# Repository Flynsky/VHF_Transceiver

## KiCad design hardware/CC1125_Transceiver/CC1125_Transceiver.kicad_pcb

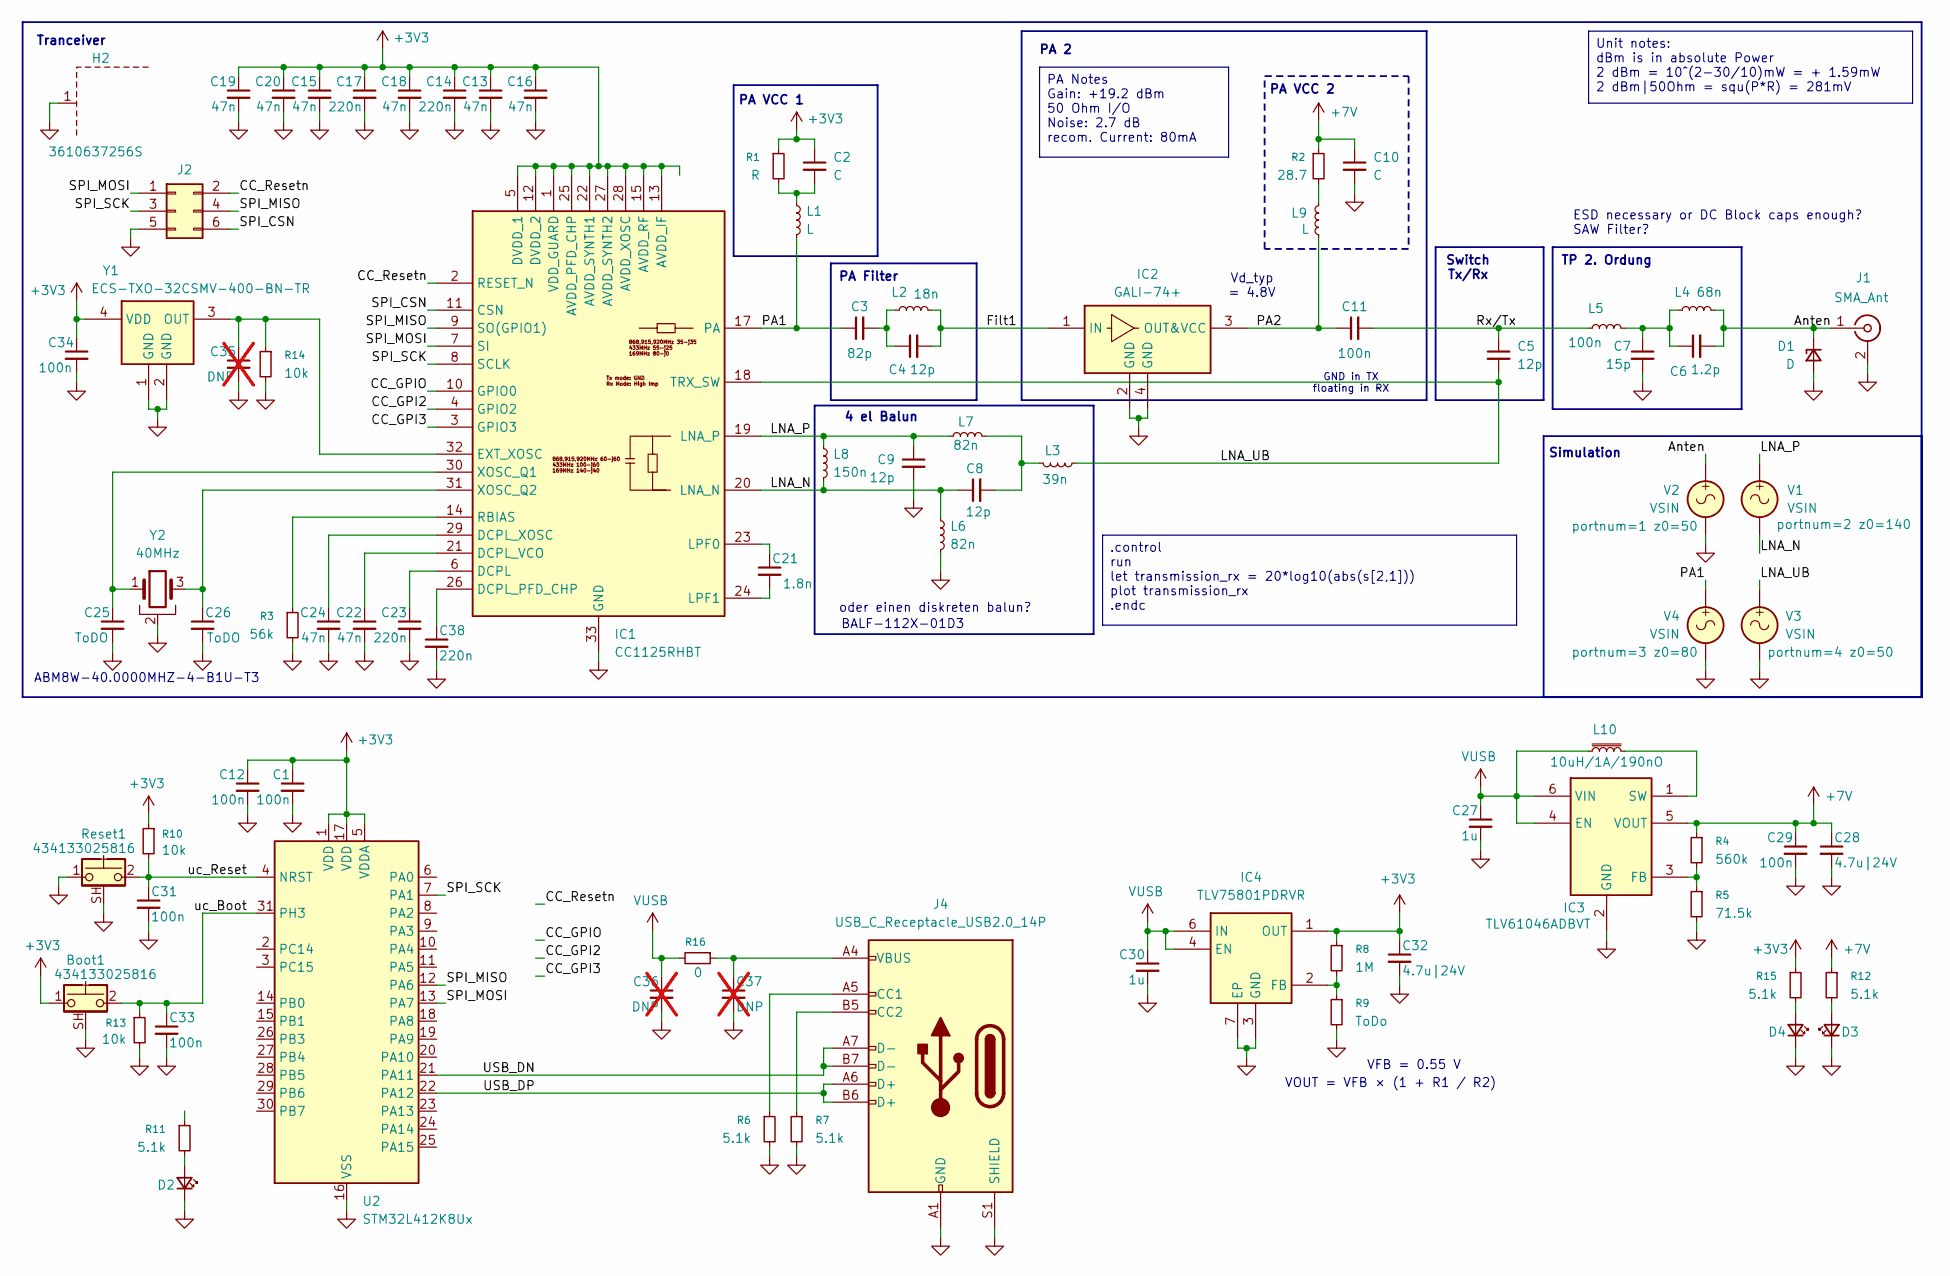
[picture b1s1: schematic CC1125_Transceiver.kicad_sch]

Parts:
Boot1: 434133025816
C1, C11, C12, C29, C31, C33, C34: 100n; C_0402_1005Metric_Pad0.74x0.62mm_HandSolder
C2, C10: C; C_0402_1005Metric_Pad0.74x0.62mm_HandSolder
C3: 82p; C_0402_1005Metric_Pad0.74x0.62mm_HandSolder
C4, C5, C8, C9: 12p; C_0402_1005Metric_Pad0.74x0.62mm_HandSolder
C6: 1.2p; C_0402_1005Metric_Pad0.74x0.62mm_HandSolder
C7: 15p; C_0402_1005Metric_Pad0.74x0.62mm_HandSolder
C13, C15, C16, C18, C19, C20, C22, C24: 47n; C_0402_1005Metric_Pad0.74x0.62mm_HandSolder
C14, C17, C23, C38: 220n; C_0402_1005Metric_Pad0.74x0.62mm_HandSolder
C21: 1.8n; C_0402_1005Metric_Pad0.74x0.62mm_HandSolder
C25, C26: ToDO; C_0402_1005Metric_Pad0.74x0.62mm_HandSolder
C27, C30: 1u; C_0402_1005Metric_Pad0.74x0.62mm_HandSolder
C28, C32: 4.7u|24V; C_0805_2012Metric_Pad1.18x1.45mm_HandSolder
C35: DNP; C_0402_1005Metric_Pad0.74x0.62mm_HandSolder; not fitted
C36, C37: DNP; C_0805_2012Metric_Pad1.18x1.45mm_HandSolder; not fitted
D1: D
D2, D3, D4: LED_0402_1005Metric_Pad0.77x0.64mm_HandSolder
H2: 3610637256S; H_Wurth_WE-SHC-SMT-FRAME_3610637256S; Part Number 3670288
IC1: CC1125RHBT; QFN50P500X500X100-33N-D; Mouser Part Number 595-CC1125RHBT
IC2: GALI-74+; GVA63; Mouser Part Number 139-GALI-74
IC3: TLV61046ADBVT; SOT95P280X145-6N; Mouser Part Number 595-TLV61046ADBVT
IC4: TLV75801PDRVR; SON65P200X200X80-7N; Mouser Part Number 595-TLV75801PDRVR
J1: SMA_Ant; SMA_Amphenol_132289_EdgeMount
J2: Conn_02x03_Counter_Clockwise; PinHeader_2x03_P1.00mm_Vertical_SMD
J4: USB_C_Receptacle_USB2.0_14P; USB421603A
L1, L9: L; L_0402_1005Metric_Pad0.77x0.64mm_HandSolder
L2: 18n; L_0402_1005Metric_Pad0.77x0.64mm_HandSolder
L3: 39n; L_0402_1005Metric_Pad0.77x0.64mm_HandSolder
L4: 68n; L_0402_1005Metric_Pad0.77x0.64mm_HandSolder
L5: 100n; L_0402_1005Metric_Pad0.77x0.64mm_HandSolder
L6, L7: 82n; L_0402_1005Metric_Pad0.77x0.64mm_HandSolder
L8: 150n; L_0402_1005Metric_Pad0.77x0.64mm_HandSolder
L10: 10uH/1A/190nO; WE-TPC_282892
R1: R; R_0402_1005Metric_Pad0.72x0.64mm_HandSolder
R2: 28.7; R_0402_1005Metric_Pad0.72x0.64mm_HandSolder
R3: 56k; R_0603_1608Metric_Pad0.98x0.95mm_HandSolder
R4: 560k; R_0402_1005Metric_Pad0.72x0.64mm_HandSolder
R5: 71.5k; R_0402_1005Metric_Pad0.72x0.64mm_HandSolder
R6, R7, R11, R12, R15: 5.1k; R_0402_1005Metric_Pad0.72x0.64mm_HandSolder
R8: 1M; R_0402_1005Metric_Pad0.72x0.64mm_HandSolder
R9: ToDo; R_0402_1005Metric_Pad0.72x0.64mm_HandSolder
R10, R13, R14: 10k; R_0603_1608Metric_Pad0.98x0.95mm_HandSolder
R16: 0; R_0603_1608Metric_Pad0.98x0.95mm_HandSolder
Reset1: 434133025816
U2: STM32L412K8Ux; QFN-32-1EP_5x5mm_P0.5mm_EP3.45x3.45mm
V1, V2, V3, V4: VSIN
Y1: ECS-TXO-32CSMV-400-BN-TR; ECSTXO32CSMV400BNTR; Mouser Part Number 520-TXO32CSMV400BNTR
Y2: 40MHz; ABM8W480000MHZ6D1XT3

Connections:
+3V3: Boot1.1, C1.1, C2.1, C12.1, C13.1, C14.1, C15.1, C16.1, C17.1, C18.1, C19.1, C20.1, C32.1, C34.1, C38.1, IC1.1 (VDD_GUARD), IC1.5 (DVDD_1), IC1.12 (DVDD_2), IC1.13 (AVDD_IF), IC1.15 (AVDD_RF), IC1.22 (AVDD_SYNTH1), IC1.25 (AVDD_PFD_CHP), IC1.26 (DCPL_PFD_CHP), IC1.27 (AVDD_SYNTH2), IC1.28 (AVDD_XOSC), IC4.1 (OUT), R1.1, R8.1, R10.1, R15.1, U2.1 (VDD), U2.5 (VDDA), U2.17 (VDD), Y1.4 (VDD)
+7V: C10.1, C28.1, C29.1, IC3.5 (VOUT), R2.1, R4.1, R12.1
/Anten: C6.2, D1.1 (K), J1.1 (In), L4.2, V2.1
/CC_GPI2: IC1.4 (GPIO2)
/CC_GPI3: IC1.3 (GPIO3)
/CC_GPIO: IC1.10 (GPIO0)
/CC_Resetn: IC1.2 (RESET_N), J2.2
/Filt1: C4.2, IC2.1 (IN), L2.2
/Filt2: C5.1, C11.2, L5.1
/LNA_N: C8.1, IC1.20 (LNA_N), L6.1, L8.2, V1.2
/LNA_P: C9.1, IC1.19 (LNA_P), L7.1, L8.1, V1.1
/LNA_UB: C5.2, IC1.18 (TRX_SW), L3.2, V3.1
/PA1: C3.1, IC1.17 (PA), L1.2, V4.1
/PA2: C11.1, IC2.3 (OUT&VCC), L9.2
/SPI_CSN: IC1.11 (CSN), J2.6
/SPI_MISO: IC1.9 (SO(GPIO1)), J2.4, U2.12 (PA6)
/SPI_MOSI: IC1.7 (SI), J2.1, U2.13 (PA7)
/SPI_SCK: IC1.8 (SCLK), J2.3, U2.7 (PA1)
/USB_DN: J4.A7 (D-), J4.B7 (D-), U2.21 (PA11)
/USB_DP: J4.A6 (D+), J4.B6 (D+), U2.22 (PA12)
/uc_Boot: Boot1.2, C33.1, R13.1, U2.31 (PH3)
/uc_Reset: C31.1, R10.2, Reset1.2, U2.4 (NRST)
GND: Boot1.SH (B), C1.2, C7.2, C9.2, C10.2, C12.2, C13.2, C14.2, C15.2, C16.2, C17.2, C18.2, C19.2, C20.2, C22.2, C23.2, C24.2, C25.2, C26.2, C27.2, C28.2, C29.2, C30.2, C31.2, C32.2, C33.2, C34.2, C35.2, C36.2, C37.2, C38.2, D1.2 (A), D2.1 (K), D3.1 (K), D4.1 (K), H2.1 (GND), IC1.33 (GND), IC2.2 (GND), IC2.4 (GND), IC3.2 (GND), IC4.3 (GND), IC4.7 (EP), J1.2 (Ext), J2.5, J4.A1 (GND), J4.A12 (GND), J4.B1 (GND), J4.B12 (GND), J4.S1 (SHIELD), L6.2, R3.2, R5.2, R6.2, R7.2, R9.2, R13.2, R14.2, Reset1.1, Reset1.SH (B), U2.16 (VSS), U2.32 (VSS), U2.33 (VSS), V2.2, V3.2, V4.2, Y1.1 (GND), Y1.2 (GND), Y2.2
unnamed: C2.2, L1.1, R1.2
unnamed: C3.2, C4.1, L2.1
unnamed: C6.1, C7.1, L4.1, L5.2
unnamed: C8.2, L3.1, L7.2
unnamed: C37.1, J4.A4 (VBUS), J4.A9 (VBUS), J4.B4 (VBUS), J4.B9 (VBUS), R16.1
unnamed: D2.2 (A), R11.2
unnamed: D3.2 (A), R12.2
unnamed: D4.2 (A), R15.2
unnamed: C23.1, IC1.6 (DCPL)
unnamed: C22.1, IC1.21 (DCPL_VCO)
unnamed: C24.1, IC1.29 (DCPL_XOSC)
unnamed: C35.1, IC1.32 (EXT_XOSC), R14.1, Y1.3 (OUT)
unnamed: C21.1, IC1.23 (LPF0)
unnamed: C21.2, IC1.24 (LPF1)
unnamed: IC1.14 (RBIAS), R3.1
unnamed: C25.1, IC1.30 (XOSC_Q1), Y2.1
unnamed: C26.1, IC1.31 (XOSC_Q2), Y2.3
unnamed: IC3.3 (FB), R4.2, R5.1
unnamed: IC3.1 (SW), L10.2
unnamed: IC4.2 (FB), R8.2, R9.1
unnamed: J4.A5 (CC1), R6.1
unnamed: J4.B5 (CC2), R7.1
unnamed: L9.1, R2.2
VUSB: C27.1, C30.1, C36.1, IC3.4 (EN), IC3.6 (VIN), IC4.4 (EN), IC4.6 (IN), L10.1, R16.2

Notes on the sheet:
PA 2
Tranceiver
Simulation
4 el Balun
PA VCC 2
Vd_typ = 4.8V
Switch Tx/Rx
TP 2. Ordung
BALF-112X-01D3
VFB = 0.55 V
ABM8W-40.0000MHZ-4-B1U-T3
GND in TX floating in RX
oder einen diskreten balun?
ESD necessary or DC Block caps enough? SAW Filter?
PA VCC 1
VOUT = VFB × (1 + R1 / R2)
PA Filter
Unit notes: dBm is in absolute Power 2 dBm = 10^(2-30/10)mW = + 1.59mW 2 dBm|50Ohm = squ(P*R) = 281mV
.control run let transmission_rx = 20*log10(abs(s[2,1])) plot transmission_rx .endc
PA Notes Gain: +19.2 dBm 50 Ohm I/O Noise: 2.7 dB recom. Current: 80mA

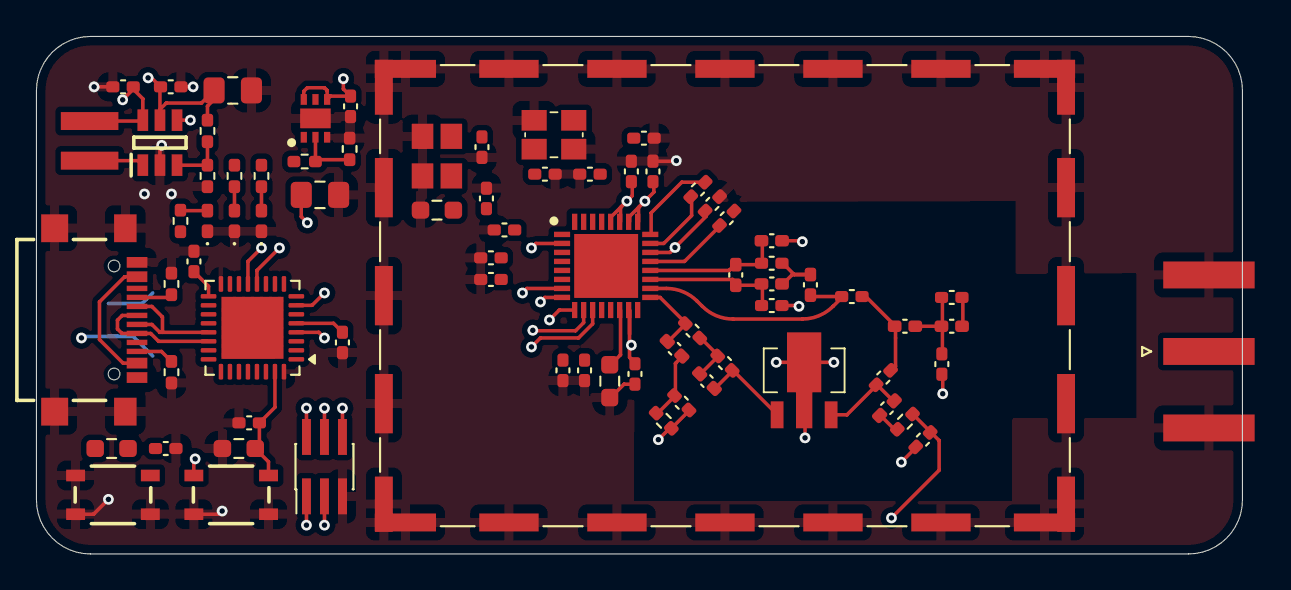
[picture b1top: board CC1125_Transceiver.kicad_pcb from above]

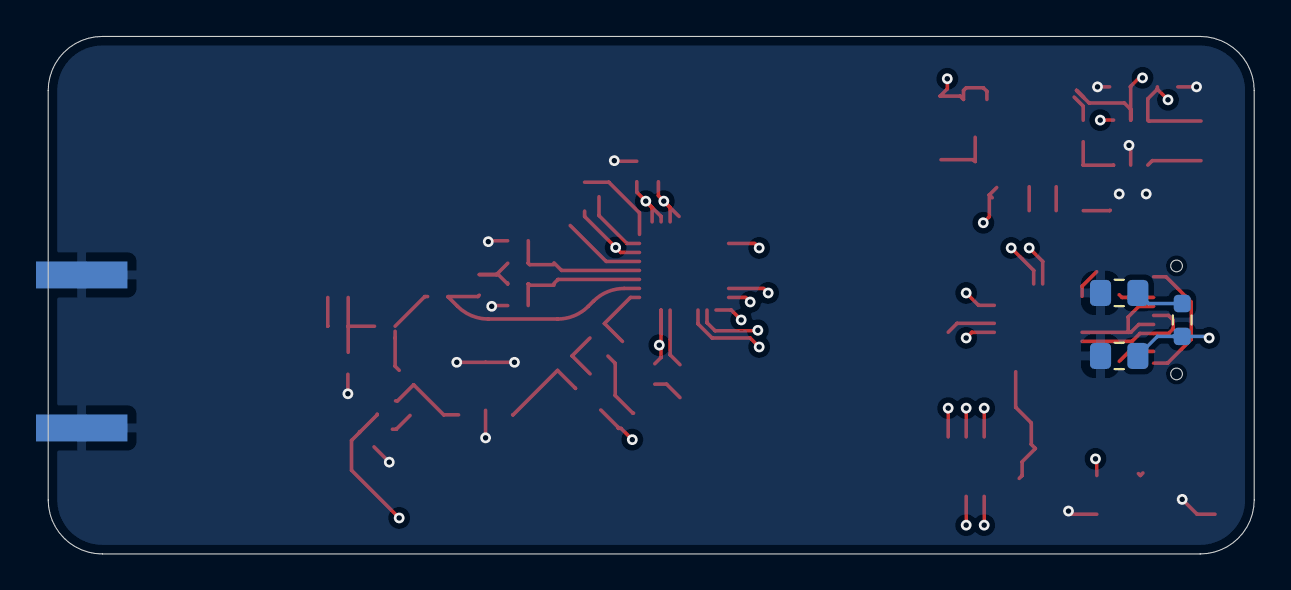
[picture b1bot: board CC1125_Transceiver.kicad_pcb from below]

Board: 4 copper layers, 67.0 x 28.8 mm, 79 parts (3 on the bottom side), 44 nets.

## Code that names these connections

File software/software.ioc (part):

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Mcu.Name=STM32L412K8Ux
Mcu.Package=UFQFPN32
Mcu.UserName=STM32L412K8Ux
PA1.Mode=Full_Duplex_Master
PA1.Signal=SPI1_SCK
PA11.Mode=Device
PA11.Signal=USB_DM
PA12.Mode=Device
PA12.Signal=USB_DP
PA6.Mode=Full_Duplex_Master
PA6.Signal=SPI1_MISO
PA7.Mode=Full_Duplex_Master
PA7.Signal=SPI1_MOSI
PH3-BOOT0\ (BOOT0).GPIOParameters=GPIO_Label
PH3-BOOT0\ (BOOT0).GPIO_Label=Boot0
PH3-BOOT0\ (BOOT0).Signal=GPIO_Output
RCC.HSE_VALUE=8000000
RCC.SYSCLKFreq_VALUE=80000000
RCC.SYSCLKSource=RCC_SYSCLKSOURCE_PLLCLK
board=custom
